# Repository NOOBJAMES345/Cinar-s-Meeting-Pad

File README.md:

# Cinar's Meeting Pad (Hack Club Blueprint)

This is a custom RP2040-based macropad designed to streamline meetings. 
It features 6 mechanical switches, a rotary encoder for volume control, and an OLED display.
The design is complete and ready for assembly once the parts are received.

## Hardware Specifications
- **Controller:** Seeed XIAO RP2040
- **Display:** 128x32 OLED (I2C)
- **Encoder:** 2-phase Rotary Encoder (No push button)
- **Switches:** 6x Mechanical Switches (Cherry MX style)

## 📦 Bill of Materials (BOM)

The following components are required for this build. The design is optimized for the parts provided by the Hack Club Blueprint grant.

| Item | Quantity | Description |
| :--- | :---: | :--- |
| **Microcontroller** | 1 | Seeed Studio XIAO RP2040 |
| **Display** | 1 | 128x32 OLED Display (I2C interface) |
| **Mechanical Switches** | 6 | MX-style switches (e.g., Gateron, Cherry) |
| **Rotary Encoder** | 1 | 3-pin Rotary Encoder (no push button) |
| **Keycaps** | 6 | Any MX-compatible keycaps |
| **PCB** | 1 | Custom designed PCB (files in `/hardware`) |
| **Connectors** | 1 | USB-C Cable (for power and data) |

*Note: In the schematic, a 128x64 OLED symbol was used due to library availability, but the physical design is tailored for a 128x32 display.*  

## Pinout
- **Buttons (SW1-6):** GP1, GP2, GP4, GP3, GP0, GP28
- **Encoder:** A: GP27, B: GP29
- **OLED:** SDA: GP6, SCL: GP7

## Firmware
The firmware is built using **KMK** on **CircuitPython**. 
The configuration is optimized for meeting shortcuts (Mute, Camera, Volume).

## 📂 Project Structure
- `/hardware`: KiCad PCB and Schematic files.
- `/firmware`: code.py (KMK Firmware configuration).
- `/case`: 3D design files for the enclosure.

## Visuals

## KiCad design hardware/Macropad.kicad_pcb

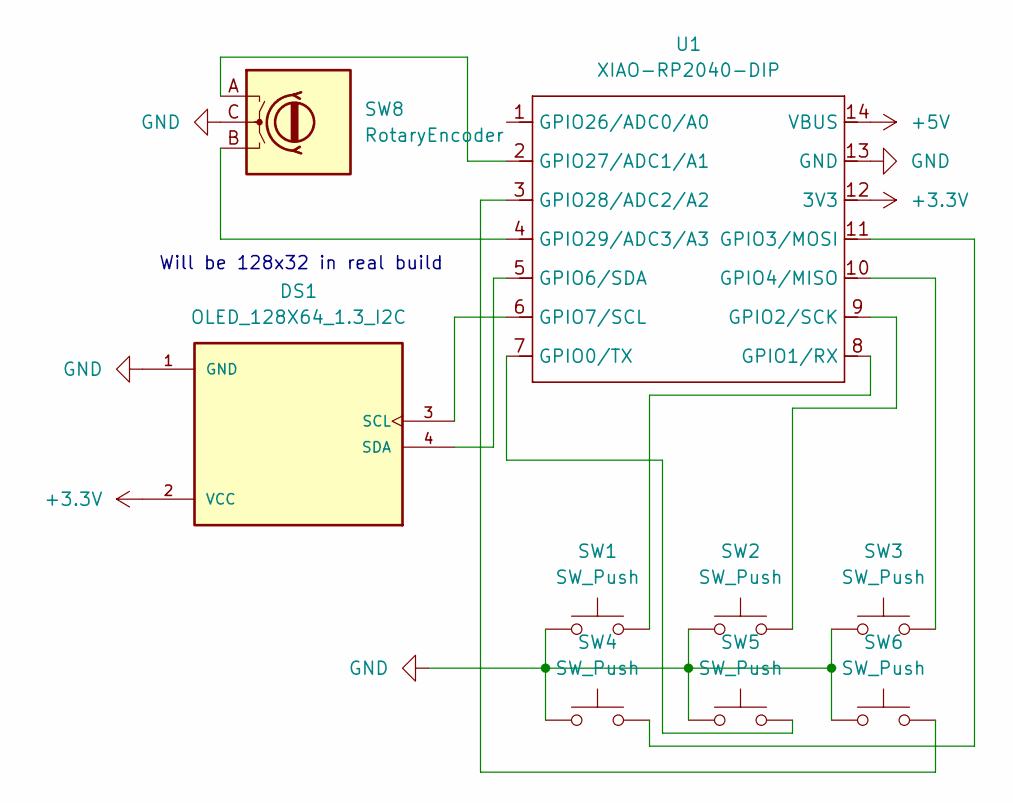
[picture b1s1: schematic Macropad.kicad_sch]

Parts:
DS1: OLED_128X64_1.3_I2C; SSD1306-0.91-OLED-4pin-128x32; PARTREV NA
SW1, SW2, SW3, SW4, SW5, SW6: SW_Push; SW_Cherry_MX_1.00u_PCB
SW8: RotaryEncoder; RotaryEncoder_Alps_EC12E_Vertical_H20mm
U1: XIAO-RP2040-DIP

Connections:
+3.3V: DS1.2 (VCC), U1.12 (3V3)
+5V: U1.14 (VBUS)
GND: DS1.1 (GND), SW1.1, SW2.1, SW3.1, SW4.1, SW5.1, SW6.1, SW8.C, U1.13 (GND)
unnamed: DS1.3 (SCL), U1.6 (GPIO7/SCL)
unnamed: DS1.4 (SDA), U1.5 (GPIO6/SDA)
unnamed: SW5.2, U1.7 (GPIO0/TX)
unnamed: SW1.2, U1.8 (GPIO1/RX)
unnamed: SW2.2, U1.9 (GPIO2/SCK)
unnamed: SW4.2, U1.11 (GPIO3/MOSI)
unnamed: SW3.2, U1.10 (GPIO4/MISO)
unnamed: SW8.A, U1.2 (GPIO27/ADC1/A1)
unnamed: SW6.2, U1.3 (GPIO28/ADC2/A2)
unnamed: SW8.B, U1.4 (GPIO29/ADC3/A3)

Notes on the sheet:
Will be 128x32 in real build

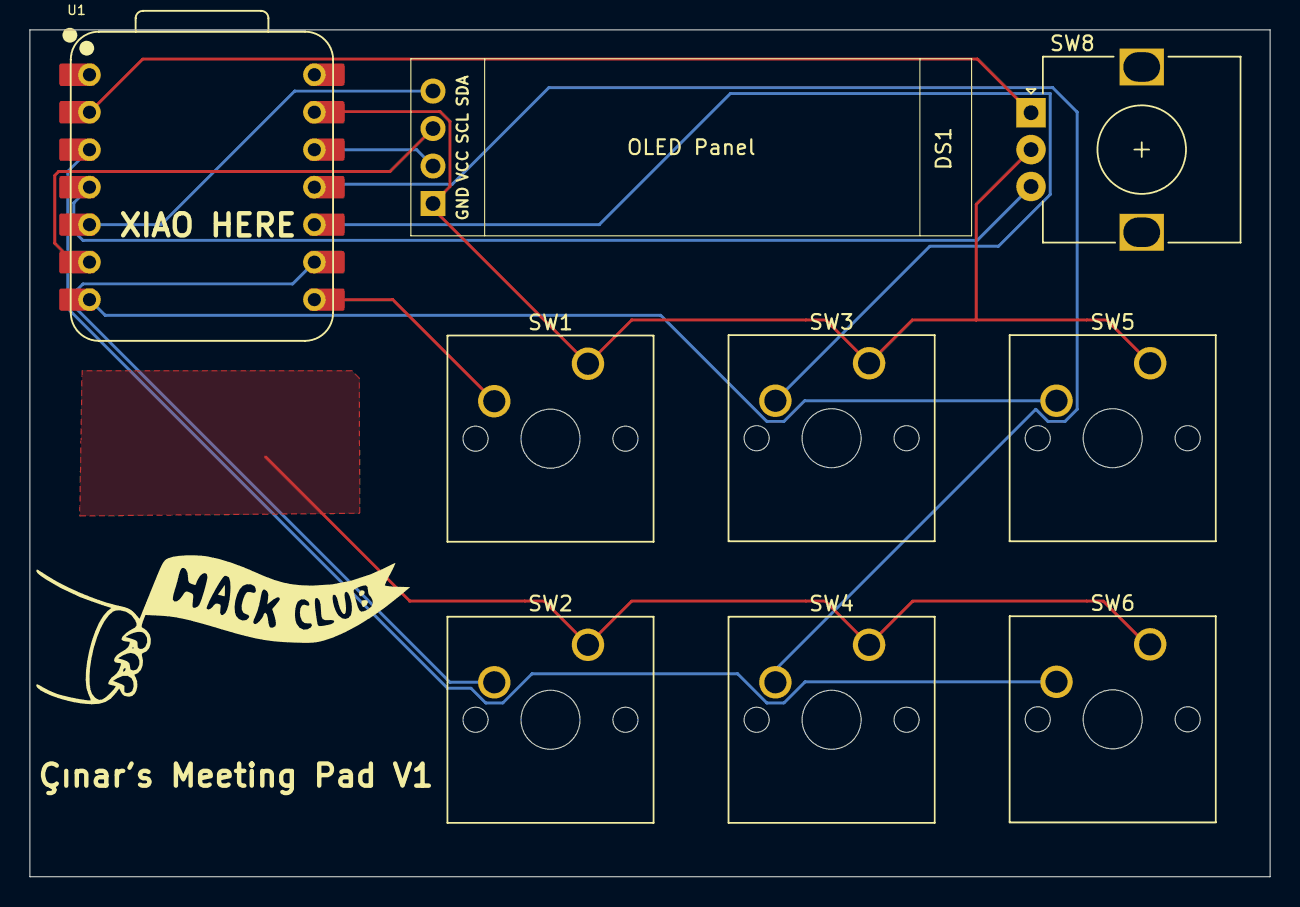
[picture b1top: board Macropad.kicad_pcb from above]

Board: 2 copper layers, 84.1 x 57.4 mm, 10 parts (0 on the bottom side), 12 nets.

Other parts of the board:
hello: LOGO; hackclub(footprint)

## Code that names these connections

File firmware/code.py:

import board
import busio
from kmk.kmk_keyboard import KMKKeyboard
from kmk.keys import KC
from kmk.scanners.keypad import KeysScanner
from kmk.modules.encoder import EncoderHandler
from kmk.extensions.display import Display, TextEntry
from kmk.extensions.media_keys import MediaKeys

keyboard = KMKKeyboard()
keyboard.modules.append(MediaKeys())

# 1. BUTON AYARLARI (Verdiğin kesin pin listesi)
keyboard.matrix = KeysScanner(
    pins=[
        board.GP1,   # SW1
        board.GP2,   # SW2
        board.GP4,   # SW3
        board.GP3,   # SW4
        board.GP0,   # SW5
        board.GP28,  # SW6
    ],
    value_when_pressed=False,
    pull=True,
)


encoder_handler = EncoderHandler()
keyboard.modules.append(encoder_handler)

# Encoder Pinleri: A=GPIO27, B=GPIO29.
encoder_handler.pins = ((board.GP27, board.GP29, None, False),)


encoder_handler.map = [
    ((KC.VOLU, KC.VOLD),), 
]

# SCL: GPIO7, SDA: GPIO6
i2c_bus = busio.I2C(board.GP7, board.GP6)

display = Display(
    display_ssd1306=None,
    width=128,
    height=32,
    brightness=0.8,
)

display.entries = [
    TextEntry(text='HackPad v1.0', x=0, y=0),
    TextEntry(text='Encoder: Aktif', x=0, y=12),
]

display_driver = display.ssd1306(i2c_bus, device_address=0x3C)
display.display = display_driver
keyboard.extensions.append(display)

# 4. TUŞ HARİTASI
keyboard.keymap = [
    [
        KC.A,           KC.B,           KC.C,           # Üst Butonlar
        KC.LCTRL(KC.C), KC.LCTRL(KC.V), KC.ENTER        # Alt Butonlar
    ]
]

if __name__ == '__main__':
    keyboard.go()

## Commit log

2025-12-28 Revise README for Cinar's Meeting Pad
    Updated project description and added hardware specifications, pinout, firmware details, and visuals.
2025-12-28 Update display specification in README
2025-12-28 Add notes on hardware to README
2025-12-28 Add project structure details to README
    Added project structure section to README.
